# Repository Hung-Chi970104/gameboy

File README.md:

# Pico Gameboy
I came across with this DIY Gameboy video made of Raspberry Pi Pico and inspired me to build my own version. The fact that RP2040 has dual-core ARM Cortex-M0+ processor makes it capable of running some light emulators. So I’ll build a little handheld game console using RP2040 that can run gameboy!
### Kirby's Dream Land 2 (My favorite)
https://github.com/user-attachments/assets/909a369a-9677-4903-9628-0e65bedbe7ed

### Tetris (my unemployed friend LMAO)
https://github.com/user-attachments/assets/1b85eab4-04bd-4f8f-a2d0-78ee750a4273

# Features
- Full-on Gameboy experience: Actually runs the classics smoothly without freaking out.
- Insanely portable: Squeezed everything into a super compact custom PCB so you can just chuck it in your pocket.
- 100% Custom Hardware: Fully designed, routed, and reflowed by yours truly (my eyes are still bleeding from staring at KiCad traces bruh).

# Components
- RP2040
- 12MHz Crystal (ABM8-272-T3)
- 8MB Flash Storage (W25Q64JVXGIQ)
- Buck-Boost Switching Regulator (RT6150B)
- USB-C (TYPE-C-31-M-12)

# PCB Designs
- 2 layers
- Single-sided component placement
- 2.6mm board thickness
- HASL (with lead) surface finish
- 1oz outer copper weight

## PCB Schematic

## PCB Layouts

## 3D Model

# How to order
- Download the zip file
- Upload the zip file to JLCPCB
- Select PCBA and continue
- Upload BOM.csv and position.csv
- Select the parts and submit payment

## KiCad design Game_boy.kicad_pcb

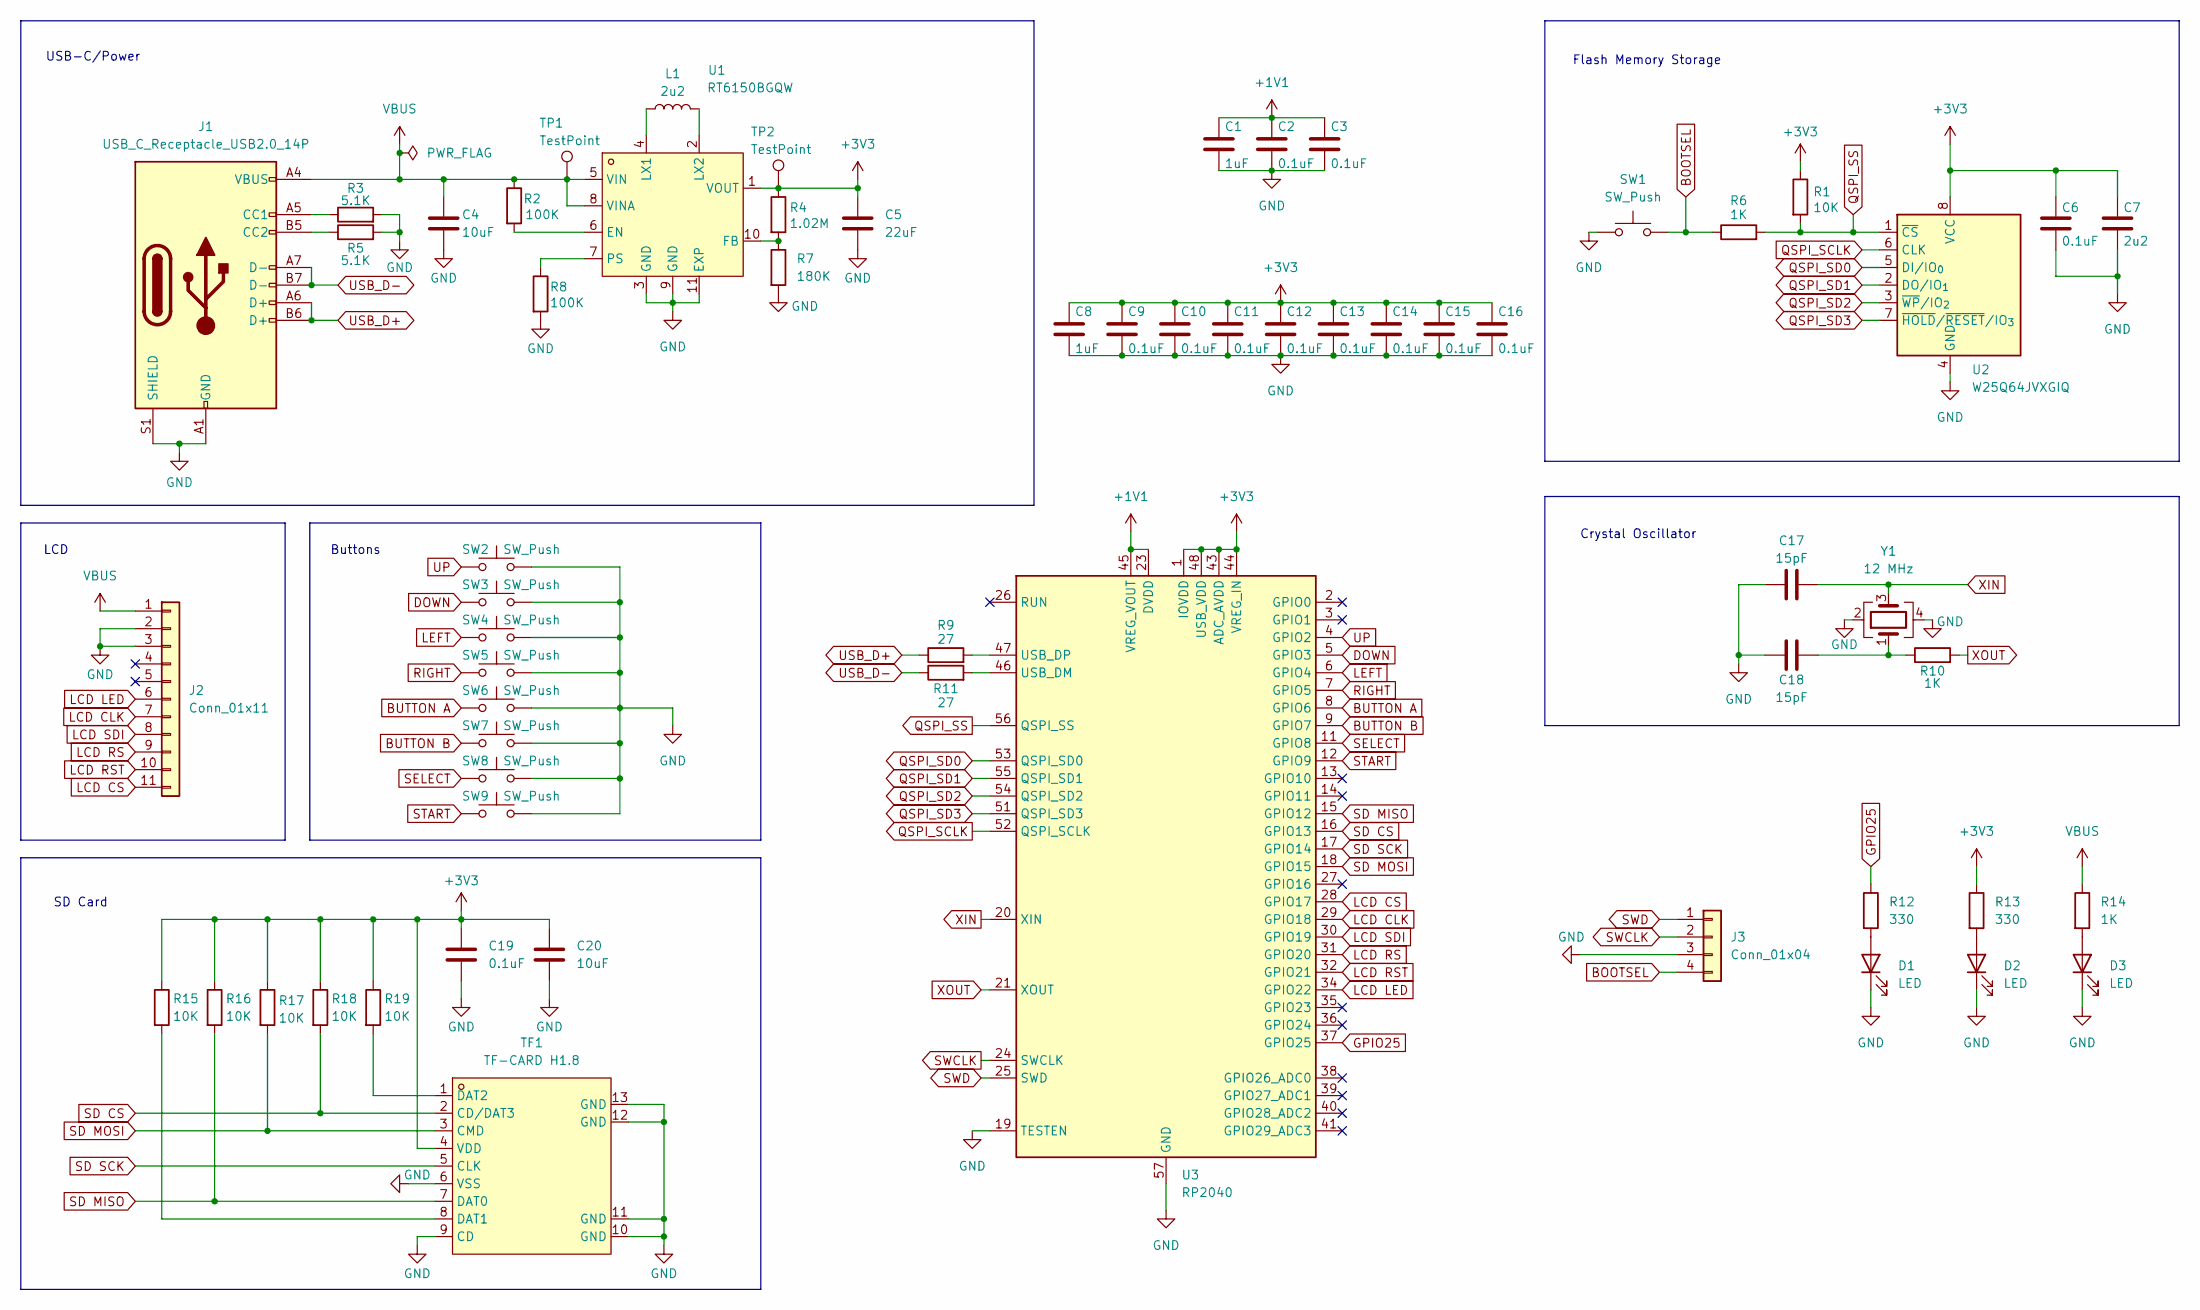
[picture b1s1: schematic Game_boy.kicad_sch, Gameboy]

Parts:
C1, C8: 1uF; C_0402_1005Metric
C2, C3, C6, C9, C10, C11, C12, C13, C14, C15, C16, C19: 0.1uF; C_0402_1005Metric
C4: 10uF; C_1206_3216Metric
C5: 22uF; C_1206_3216Metric
C7: 2u2; C_0603_1608Metric
C17, C18: 15pF; C_0402_1005Metric
C20: 10uF; C_0603_1608Metric
D1, D2, D3: LED; LED_0805_2012Metric
J1: USB_C_Receptacle_USB2.0_14P; USB_C_Receptacle_HRO_TYPE-C-31-M-12
J2: Conn_01x11; PinHeader_1x11_P2.54mm_Vertical
J3: Conn_01x04; PinHeader_1x04_P2.54mm_Vertical
L1: 2u2; IND-SMD_L4.0-W4.0_XAL4030-332MEC
R1, R15, R16, R17, R18, R19: 10K; R_0402_1005Metric
R2, R8: 100K; R_0402_1005Metric
R3, R5: 5.1K; R_0402_1005Metric
R4: 1.02M; R_0402_1005Metric
R6, R10: 1K; R_0402_1005Metric
R7: 180K; R_0402_1005Metric
R9, R11: 27; R_0402_1005Metric
R12, R13: 330; R_0805_2012Metric
R14: 1K; R_0805_2012Metric
SW1, SW8, SW9: SW_Push; SW_Push_SPST_NO_Alps_SKRK
SW2, SW3, SW4, SW5, SW6, SW7: SW_Push; SW_PUSH_6mm
TF1: TF-CARD H1.8; TF-SMD_TF-CARD-H1.8; LCSC Part C7529389
TP1, TP2: TestPoint; TestPoint_Pad_1.0x1.0mm
U1: RT6150BGQW; WSON-10_L2.5-W2.5-P0.50-BL-EP; LCSC Part C147972
U2: W25Q64JVXGIQ; XSON-8_L4.0-W4.0-P0.80-TL-EP
U3: RP2040; QFN-56-1EP_7x7mm_P0.4mm_EP3.2x3.2mm
Y1: 12 MHz; Crystal_SMD_3225-4Pin_3.2x2.5mm

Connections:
+1V1: C1.1, C2.1, C3.1, U3.23 (DVDD), U3.45 (VREG_VOUT), U3.50 (DVDD)
+3V3: C5.1, C6.1, C7.1, C8.1, C9.1, C10.1, C11.1, C12.1, C13.1, C14.1, C15.1, C16.1, C19.1, C20.1, R1.1, R4.1, R13.1, R15.1, R16.1, R17.1, R18.1, R19.1, TF1.4 (VDD), TP2.1, U1.1 (VOUT), U2.8 (VCC), U3.1 (IOVDD), U3.10 (IOVDD), U3.22 (IOVDD), U3.33 (IOVDD), U3.42 (IOVDD), U3.43 (ADC_AVDD), U3.44 (VREG_IN), U3.48 (USB_VDD), U3.49 (IOVDD)
BOOTSEL: J3.4, R6.1, SW1.2
BUTTON A: SW6.1, U3.8 (GPIO6)
BUTTON B: SW7.1, U3.9 (GPIO7)
DOWN: SW3.1, U3.5 (GPIO3)
GND: C1.2, C2.2, C3.2, C4.2, C5.2, C6.2, C7.2, C8.2, C9.2, C10.2, C11.2, C12.2, C13.2, C14.2, C15.2, C16.2, C17.1, C18.1, C19.2, C20.2, D1.1 (K), D2.1 (K), D3.1 (K), J1.A1 (GND), J1.A12 (GND), J1.B1 (GND), J1.B12 (GND), J1.S1 (SHIELD), J2.2, J2.3, J3.3, R3.2, R5.2, R7.2, R8.2, SW1.1, SW2.2, SW3.2, SW4.2, SW5.2, SW6.2, SW7.2, SW8.2, SW9.2, TF1.6 (VSS), TF1.9 (CD), TF1.10 (GND), TF1.11 (GND), TF1.12 (GND), TF1.13 (GND), U1.3 (GND), U1.9 (GND), U1.11 (EXP), U2.4 (GND), U3.19 (TESTEN), U3.57 (GND), Y1.2, Y1.4
GPIO25: R12.1, U3.37 (GPIO25)
LCD CLK: J2.7, U3.29 (GPIO18)
LCD CS: J2.11, U3.28 (GPIO17)
LCD LED: J2.6, U3.34 (GPIO22)
LCD RS: J2.9, U3.31 (GPIO20)
LCD RST: J2.10, U3.32 (GPIO21)
LCD SDI: J2.8, U3.30 (GPIO19)
LEFT: SW4.1, U3.6 (GPIO4)
unnamed: C18.2, R10.1, Y1.1
unnamed: D1.2 (A), R12.2
unnamed: D2.2 (A), R13.2
unnamed: D3.2 (A), R14.2
unnamed: J1.A5 (CC1), R3.1
unnamed: J1.B5 (CC2), R5.1
unnamed: R15.2, TF1.8 (DAT1)
unnamed: R19.2, TF1.1 (DAT2)
unnamed: R2.2, U1.6 (EN)
unnamed: R4.2, R7.1, U1.10 (FB)
unnamed: L1.1, U1.4 (LX1)
unnamed: L1.2, U1.2 (LX2)
unnamed: R8.1, U1.7 (PS)
unnamed: R11.2, U3.46 (USB_DM)
unnamed: R9.2, U3.47 (USB_DP)
QSPI_SCLK: U2.6 (CLK), U3.52 (QSPI_SCLK)
QSPI_SD0: U2.5 (DI/IO_{0}), U3.53 (QSPI_SD0)
QSPI_SD1: U2.2 (DO/IO_{1}), U3.55 (QSPI_SD1)
QSPI_SD2: U2.3 (~WP/IO_{2}), U3.54 (QSPI_SD2)
QSPI_SD3: U2.7 (~HOLD/~RESET/IO_{3}), U3.51 (QSPI_SD3)
QSPI_SS: R1.2, R6.2, U2.1 (~CS), U3.56 (QSPI_SS)
RIGHT: SW5.1, U3.7 (GPIO5)
SD CS: R18.2, TF1.2 (CD/DAT3), U3.16 (GPIO13)
SD MISO: R16.2, TF1.7 (DAT0), U3.15 (GPIO12)
SD MOSI: R17.2, TF1.3 (CMD), U3.18 (GPIO15)
SD SCK: TF1.5 (CLK), U3.17 (GPIO14)
SELECT: SW8.1, U3.11 (GPIO8)
START: SW9.1, U3.12 (GPIO9)
SWCLK: J3.2, U3.24 (SWCLK)
SWD: J3.1, U3.25 (SWD)
UP: SW2.1, U3.4 (GPIO2)
USB_D+: J1.A6 (D+), J1.B6 (D+), R9.1
USB_D-: J1.A7 (D-), J1.B7 (D-), R11.1
VBUS: C4.1, J1.A4 (VBUS), J1.A9 (VBUS), J1.B4 (VBUS), J1.B9 (VBUS), J2.1, R2.1, R14.1, TP1.1, U1.5 (VIN), U1.8 (VINA)
XIN: C17.2, U3.20 (XIN), Y1.3
XOUT: R10.2, U3.21 (XOUT)

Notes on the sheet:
LCD
SD Card
Flash Memory Storage
USB-C/Power
Crystal Oscillator
Buttons

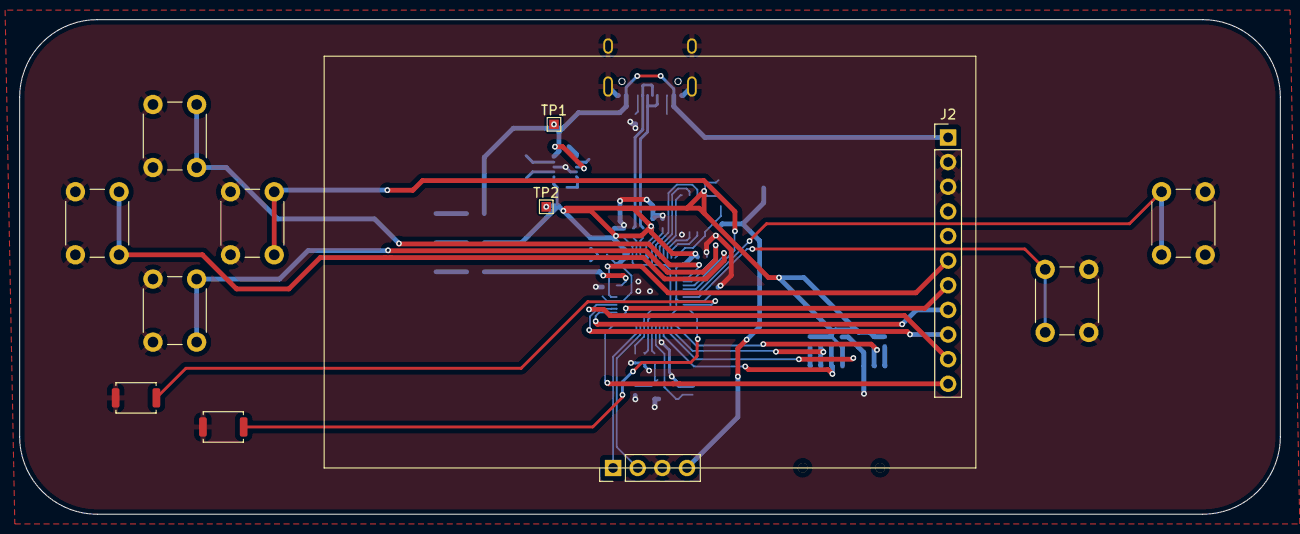
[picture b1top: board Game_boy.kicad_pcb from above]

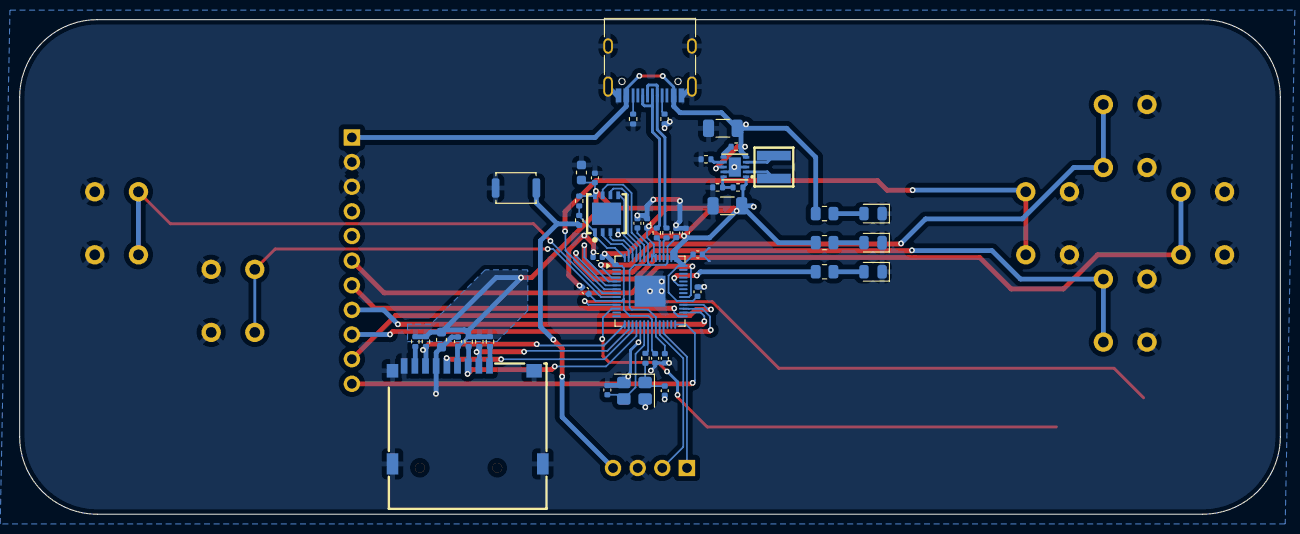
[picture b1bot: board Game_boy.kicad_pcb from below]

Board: 2 copper layers, 130.0 x 51.0 mm, 60 parts (48 on the bottom side), 51 nets.

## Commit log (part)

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2026-04-25 Update Demo
2026-04-25 Fix video demo
2026-04-25 Update demo video reference in README
    Replaced video embed with a link to the demo video.
2026-04-26 Readme Update
2026-04-26 Update README with additional resource link
    Added a new link to the README for additional resources.
